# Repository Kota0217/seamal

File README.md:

# seamal
水中用マイクロロボット開発用リポジトリ

## リンク集
### マイコン関係
* [データシート](https://akizukidenshi.com/download/ds/st/stm32f303x6_st32f303x8.pdf) (ピン配置はp.29)
* [タイマー割り込みについて](https://mia-0032.hatenablog.jp/entry/mbed-os-events-library)
* 開発環境はMbed Studio 
  * mbed os 6.3.0で動作確認を行う (2021/07/27 石関)

## 作業記録

### 2021/07/27 (火)　石関記録
* EventQueueのcall_everyで割り込み処理を行うコードを書いたが、割り込みとmainのwhile(1)が同時に実行されない
  * dispatchをwhileより前に置くと、割り込み処理だけ回る
  * dispatchをwhileより後に置くと、whileだけ回る

### 2021/07/26 (月)　石関記録
* stm32f303k8を入手し、変換基板にはんだ付けした
* stm32f030 nucleo64を使ってプログラムを書き込んだ
  * 開発環境　Mbed Studio
  * Lチカを行うプログラムを書き込んだ
* 動作を確認した
* デバッガーのTX,RXのピンをf303k8に接続したら、UART通信ができた

### 2021/07/25 (日)　石関記録
* Arudiono IDE上でボードマネージャーからstmのライブラリをインストールした

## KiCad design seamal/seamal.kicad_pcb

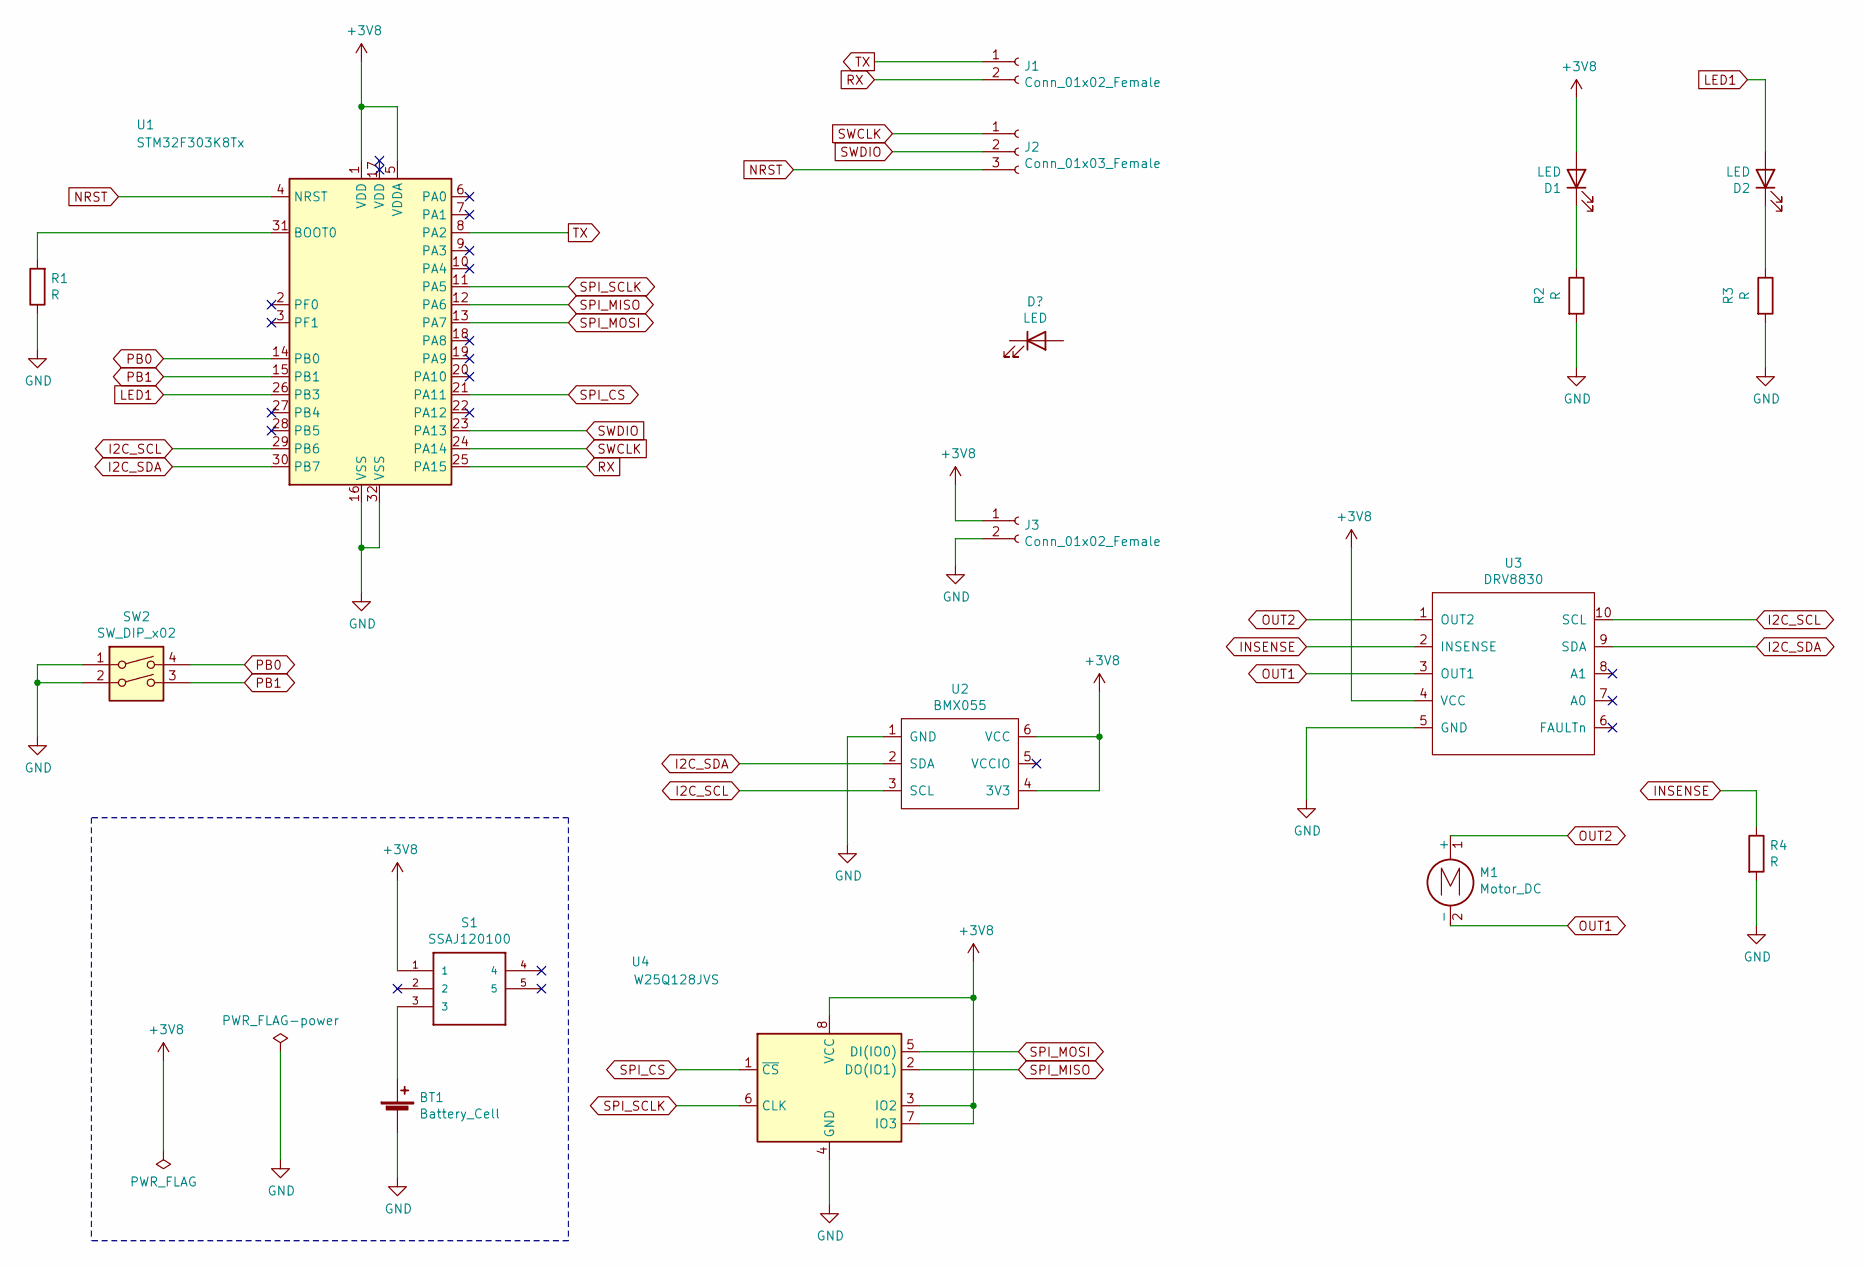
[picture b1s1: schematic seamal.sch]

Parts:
BT1: Battery_Cell; R_0805_2012Metric_Pad1.20x1.40mm_HandSolder
D1, D2: LED; LED_0603_1608Metric_Pad1.05x0.95mm_HandSolder
J1, J3: Conn_01x02_Female; PinSocket_1x02_P2.00mm_Vertical
J2: Conn_01x03_Female; PinSocket_1x03_P2.00mm_Vertical
M1: Motor_DC; R_0805_2012Metric_Pad1.20x1.40mm_HandSolder
R1, R2, R3, R4: R; R_0805_2012Metric_Pad1.20x1.40mm_HandSolder
S1: SSAJ120100; Mouser_Part_Number 688-SSAJ120100
SW2: SW_DIP_x02; SW_DIP_SPSTx02_Slide_KingTek_DSHP02TS_W7.62mm_P1.27mm
U1: STM32F303K8Tx; LQFP-32_7x7mm_P0.8mm
U2: BMX055
U3: DRV8830; DRV8830DGQ
U4: W25Q128JVS; SOIC-8_5.23x5.23mm_P1.27mm

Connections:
+3V8: D1.2 (A), J3.1, S1.1, U1.1 (VDD), U1.5 (VDDA), U2.4 (3V3), U2.6 (VCC), U3.4 (VCC), U4.3 (IO2), U4.7 (IO3), U4.8 (VCC)
GND: BT1.2 (-), J3.2, R1.1, R2.2, R3.2, R4.2, SW2.1, SW2.2, U1.16 (VSS), U1.32 (VSS), U2.1 (GND), U3.5 (GND), U4.4 (GND)
I2C_SCL: U1.29 (PB6), U2.3 (SCL), U3.10 (SCL)
I2C_SDA: U1.30 (PB7), U2.2 (SDA), U3.9 (SDA)
INSENSE: R4.1, U3.2 (INSENSE)
LED1: D2.2 (A), U1.26 (PB3)
NRST: J2.3, U1.4 (NRST)
unnamed: BT1.1 (+), S1.3
unnamed: D1.1 (K), R2.1
unnamed: D2.1 (K), R3.1
unnamed: R1.2, U1.31 (BOOT0)
OUT1: M1.2 (-), U3.3 (OUT1); also elsewhere on the board
OUT2: M1.1 (+), U3.1 (OUT2); also elsewhere on the board
PB0: SW2.4, U1.14 (PB0)
PB1: SW2.3, U1.15 (PB1)
RX: J1.2, U1.25 (PA15)
SPI_CS: U1.21 (PA11), U4.1 (~CS)
SPI_MISO: U1.12 (PA6), U4.2 (DO(IO1))
SPI_MOSI: U1.13 (PA7), U4.5 (DI(IO0))
SPI_SCLK: U1.11 (PA5), U4.6 (CLK)
SWCLK: J2.1, U1.24 (PA14)
SWDIO: J2.2, U1.23 (PA13)
TX: J1.1, U1.8 (PA2)

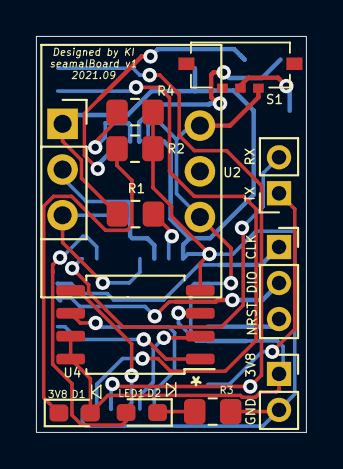
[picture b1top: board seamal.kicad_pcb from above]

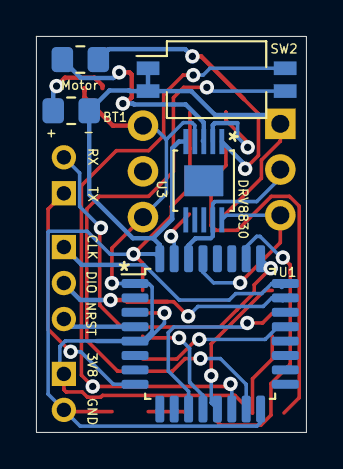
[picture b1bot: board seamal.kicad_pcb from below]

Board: 2 copper layers, 15.0 x 22.0 mm, 17 parts (5 on the bottom side), 23 nets.

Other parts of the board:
Motor: Motor_DC; R_0805_2012Metric_Pad1.20x1.40mm_HandSolder

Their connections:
OUT1: Motor.2; also elsewhere on the board
OUT2: Motor.1; also elsewhere on the board

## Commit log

2021-07-25 作業記録の更新
2021-07-26 記録を追記
2021-07-27 作業履歴を更新
2021-07-27 記録更新
2021-09-12 Delete main.cpp
    delete
2021-10-22 test
2021-10-22 delete
2021-10-22 board_info
2021-10-22 deleted
2021-10-22 test1

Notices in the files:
parts and their libraries:
Copyright 2021 Accelerated Designs. All rights reserved.
